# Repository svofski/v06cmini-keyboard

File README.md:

# A miniature keyboard for Vector-06c

The keyboard is a miniature full-functioning replica of Vector-06c keyboard. Its dimensions are 150x55mm. 
It can be connected as a replacement keyboard to the real Vector-06c, or it can be used as a USB HID keyboard with a Vector-06c emulator or FPGA implementation.
It can also be connected to v06c-esp vector-06c-mini.

The design files comprise 3 parts. 

 1. [Key caps](blender) A high resolution mesh with legend engraving designed in blender
 2. [Bottom PCB](kicad/v06ckeyboard) carries the switches and an optional Pi Pico for connectivity
 3. [Top PCB](kicad/v06ckeyboard) a frame that holds the keycaps in place

This keyboard is very small indeed.

## Firmware

### spislave

[spislave](firmware/spislave) is the main intended use with [v06x-mini](https://github.com/svofski/v06x-tiny).

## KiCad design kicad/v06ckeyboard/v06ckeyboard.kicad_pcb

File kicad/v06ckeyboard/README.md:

# vector-06c-mini keyboard PCBs

Main PCB and keycaps frame.

Explore using [kicanvas](https://kicanvas.org/?github=https%3A%2F%2Fgithub.com%2Fsvofski%2Fv06cmini-keyboard%2Ftree%2Fmaster%2Fkicad%2Fv06ckeyboard).

[PDF schematic](/kicad/v06ckeyboard/v06c-mini-keyboard.pdf)

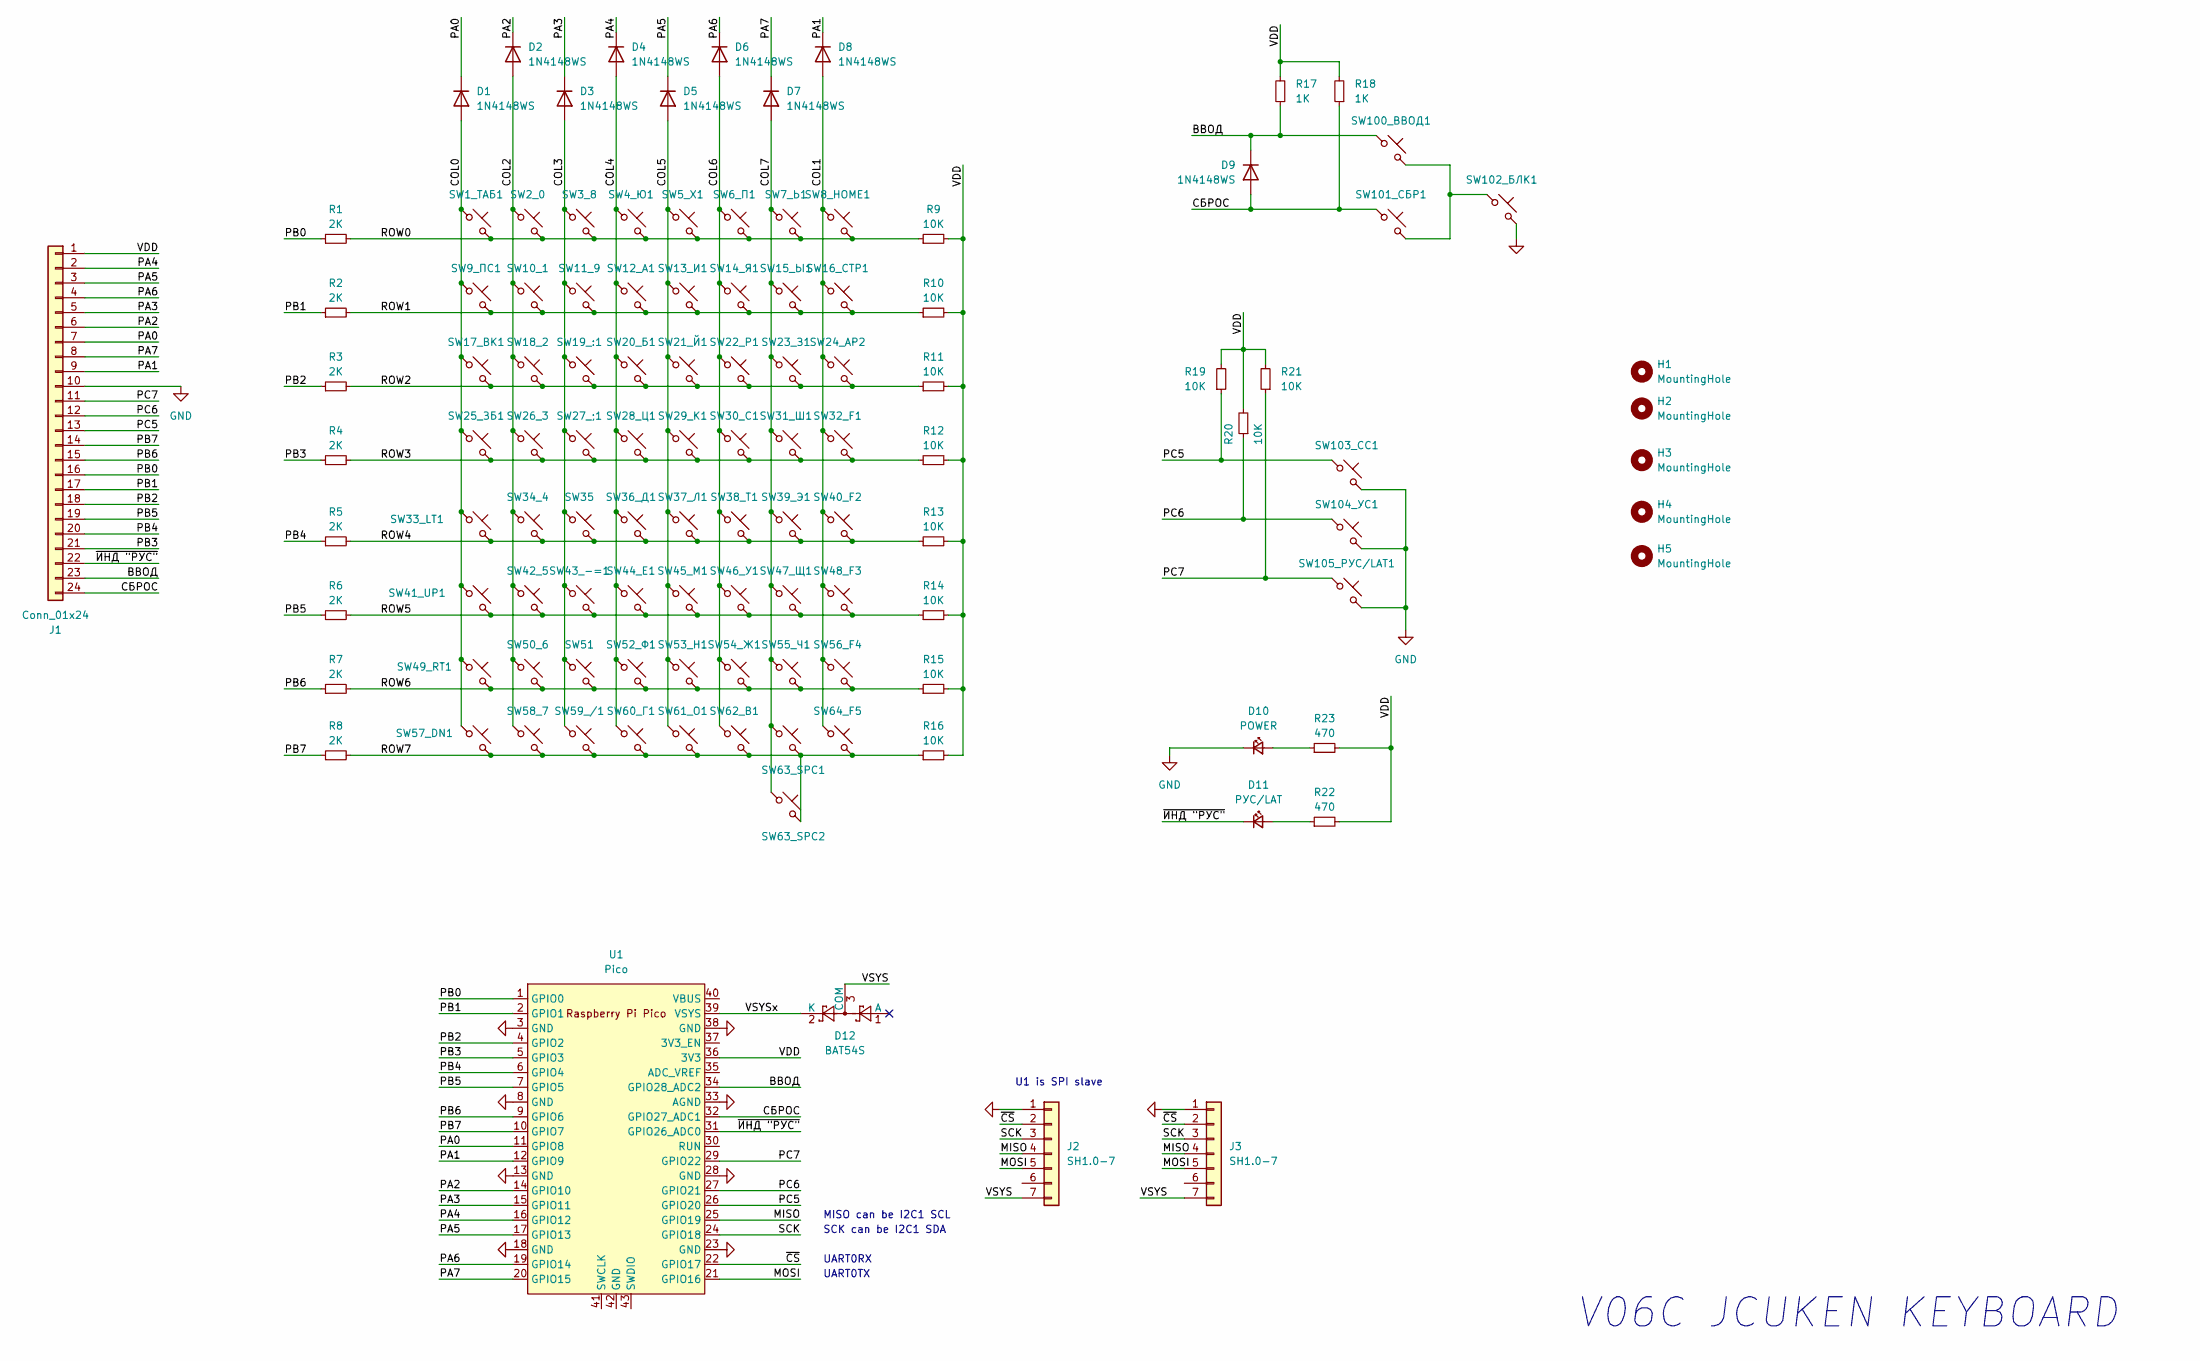
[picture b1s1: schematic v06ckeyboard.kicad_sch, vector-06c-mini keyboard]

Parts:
D1, D2, D3, D4, D5, D6, D7, D8, D9: 1N4148WS; D_SOD-323; LCSC C2128
D10: POWER; LED_0805_2012Metric
D11: РУС/LAT; LED_0805_2012Metric
D12: BAT54S; SOT-23
H1, H2, H3, H4, H5: MountingHole; MountingHole_3.2mm_M3
J1: Conn_01x24; PinHeader_1x24_P2.54mm_Horizontal
J2: SH1.0-7; PinHeader_1x07_P2.54mm_Vertical
J3: SH1.0-7; JST_SH_SM07B-SRSS-TB_1x07-1MP_P1.00mm_Horizontal
R1, R2, R3, R4, R5, R6, R7, R8: 2K; R_0603_1608Metric
R9, R10, R11, R12, R13, R14, R15, R16, R19, R20, R21: 10K; R_0603_1608Metric
R17, R18: 1K; R_0603_1608Metric
R22, R23: 470; R_0603_1608Metric
SW1_ТАБ1, SW2_0, SW3_8, SW4_Ю1, SW5_Х1, SW6_П1, SW7_Ь1, SW8_HOME1, SW9_ПС1, SW10_1, SW11_9, SW12_А1, SW13_И1, SW14_Я1, SW15_Ы1, SW16_СТР1, SW17_ВК1, SW18_2, SW19_:1, SW20_Б1, SW21_Й1, SW22_Р1, SW23_З1, SW24_AP2, SW25_ЗБ1, SW26_3, SW27_;1, SW28_Ц1, SW29_К1, SW30_С1, SW31_Ш1, SW32_F1, SW33_LT1, SW34_4, SW35, SW36_Д1, SW37_Л1, SW38_Т1, SW39_Э1, SW40_F2, SW41_UP1, SW42_5, SW43_-=1, SW44_E1, SW45_М1, SW46_У1, SW47_Щ1, SW48_F3, SW49_RT1, SW50_6, SW51, SW52_Ф1, SW53_Н1, SW54_Ж1, SW55_Ч1, SW56_F4, SW57_DN1, SW58_7, SW59_/1, SW60_Г1, SW61_О1, SW62_В1, SW63_SPC1, SW63_SPC2, SW64_F5, SW100_ВВОД1, SW101_СБР1, SW102_БЛК1, SW103_СС1, SW104_УС1, SW105_РУС/LAT1: SKPMAME010; SKPM; LCSC C115348
U1: Pico; RPi_Pico_SMD_TH

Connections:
/COL0: D1.2 (A), SW1_ТАБ1.1, SW9_ПС1.1, SW17_ВК1.1, SW25_ЗБ1.1, SW33_LT1.1, SW41_UP1.1, SW49_RT1.1, SW57_DN1.1
/COL1: D8.2 (A), SW8_HOME1.1, SW16_СТР1.1, SW24_AP2.1, SW32_F1.1, SW40_F2.1, SW48_F3.1, SW56_F4.1, SW64_F5.1
/COL2: D2.2 (A), SW2_0.1, SW10_1.1, SW18_2.1, SW26_3.1, SW34_4.1, SW42_5.1, SW50_6.1, SW58_7.1
/COL3: D3.2 (A), SW3_8.1, SW11_9.1, SW19_:1.1, SW27_;1.1, SW35.1, SW43_-=1.1, SW51.1, SW59_/1.1
/COL4: D4.2 (A), SW4_Ю1.1, SW12_А1.1, SW20_Б1.1, SW28_Ц1.1, SW36_Д1.1, SW44_E1.1, SW52_Ф1.1, SW60_Г1.1
/COL5: D5.2 (A), SW5_Х1.1, SW13_И1.1, SW21_Й1.1, SW29_К1.1, SW37_Л1.1, SW45_М1.1, SW53_Н1.1, SW61_О1.1
/COL6: D6.2 (A), SW6_П1.1, SW14_Я1.1, SW22_Р1.1, SW30_С1.1, SW38_Т1.1, SW46_У1.1, SW54_Ж1.1, SW62_В1.1
/COL7: D7.2 (A), SW7_Ь1.1, SW15_Ы1.1, SW23_З1.1, SW31_Ш1.1, SW39_Э1.1, SW47_Щ1.1, SW55_Ч1.1, SW63_SPC1.1, SW63_SPC2.1
/MISO: J2.4, J3.4, U1.25 (GPIO19)
/MOSI: J2.5, J3.5, U1.21 (GPIO16)
/PA0: D1.1 (K), J1.7, U1.11 (GPIO8)
/PA1: D8.1 (K), J1.9, U1.12 (GPIO9)
/PA2: D2.1 (K), J1.6, U1.14 (GPIO10)
/PA3: D3.1 (K), J1.5, U1.15 (GPIO11)
/PA4: D4.1 (K), J1.2, U1.16 (GPIO12)
/PA5: D5.1 (K), J1.3, U1.17 (GPIO13)
/PA6: D6.1 (K), J1.4, U1.19 (GPIO14)
/PA7: D7.1 (K), J1.8, U1.20 (GPIO15)
/PB0: J1.16, R1.1, U1.1 (GPIO0)
/PB1: J1.17, R2.1, U1.2 (GPIO1)
/PB2: J1.18, R3.1, U1.4 (GPIO2)
/PB3: J1.21, R4.1, U1.5 (GPIO3)
/PB4: J1.20, R5.1, U1.6 (GPIO4)
/PB5: J1.19, R6.1, U1.7 (GPIO5)
/PB6: J1.15, R7.1, U1.9 (GPIO6)
/PB7: J1.14, R8.1, U1.10 (GPIO7)
/PC5: J1.13, R19.1, SW103_СС1.1, U1.26 (GPIO20)
/PC6: J1.12, R20.1, SW104_УС1.1, U1.27 (GPIO21)
/PC7: J1.11, R21.1, SW105_РУС/LAT1.1, U1.29 (GPIO22)
/ROW0: R1.2, R9.1, SW1_ТАБ1.2, SW2_0.2, SW3_8.2, SW4_Ю1.2, SW5_Х1.2, SW6_П1.2, SW7_Ь1.2, SW8_HOME1.2
/ROW1: R2.2, R10.1, SW9_ПС1.2, SW10_1.2, SW11_9.2, SW12_А1.2, SW13_И1.2, SW14_Я1.2, SW15_Ы1.2, SW16_СТР1.2
/ROW2: R3.2, R11.1, SW17_ВК1.2, SW18_2.2, SW19_:1.2, SW20_Б1.2, SW21_Й1.2, SW22_Р1.2, SW23_З1.2, SW24_AP2.2
/ROW3: R4.2, R12.1, SW25_ЗБ1.2, SW26_3.2, SW27_;1.2, SW28_Ц1.2, SW29_К1.2, SW30_С1.2, SW31_Ш1.2, SW32_F1.2
/ROW4: R5.2, R13.1, SW33_LT1.2, SW34_4.2, SW35.2, SW36_Д1.2, SW37_Л1.2, SW38_Т1.2, SW39_Э1.2, SW40_F2.2
/ROW5: R6.2, R14.1, SW41_UP1.2, SW42_5.2, SW43_-=1.2, SW44_E1.2, SW45_М1.2, SW46_У1.2, SW47_Щ1.2, SW48_F3.2
/ROW6: R7.2, R15.1, SW49_RT1.2, SW50_6.2, SW51.2, SW52_Ф1.2, SW53_Н1.2, SW54_Ж1.2, SW55_Ч1.2, SW56_F4.2
/ROW7: R8.2, R16.1, SW57_DN1.2, SW58_7.2, SW59_/1.2, SW60_Г1.2, SW61_О1.2, SW62_В1.2, SW63_SPC1.2, SW63_SPC2.2, SW64_F5.2
/SCK: J2.3, J3.3, U1.24 (GPIO18)
/VDD: J1.1, R9.2, R10.2, R11.2, R12.2, R13.2, R14.2, R15.2, R16.2, R17.2, R18.2, R19.2, R20.2, R21.2, R22.2, R23.2, U1.36 (3V3)
/VSYS: D12.3 (COM), J2.7, J3.7
/VSYSx: D12.2 (K), U1.39 (VSYS)
/~CS: J2.2, J3.2, U1.22 (GPIO17)
/~ИНД "РУС": D11.1 (K), J1.22, U1.31 (GPIO26_ADC0)
/ВВОД: D9.1 (K), J1.23, R17.1, SW100_ВВОД1.1, U1.34 (GPIO28_ADC2)
/СБРОС: D9.2 (A), J1.24, R18.1, SW101_СБР1.1, U1.32 (GPIO27_ADC1)
GND: D10.1 (K), J1.10, J2.1, J3.1, SW102_БЛК1.2, SW103_СС1.2, SW104_УС1.2, SW105_РУС/LAT1.2, U1.3 (GND), U1.8 (GND), U1.13 (GND), U1.18 (GND), U1.23 (GND), U1.28 (GND), U1.33 (AGND), U1.38 (GND)
unnamed: D10.2 (A), R23.1
unnamed: D11.2 (A), R22.1
unnamed: SW100_ВВОД1.2, SW101_СБР1.2, SW102_БЛК1.1

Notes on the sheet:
V06C JCUKEN KEYBOARD
UART0TX
MISO can be I2C1 SCL
UART0RX
SCK can be I2C1 SDA
U1 is SPI slave

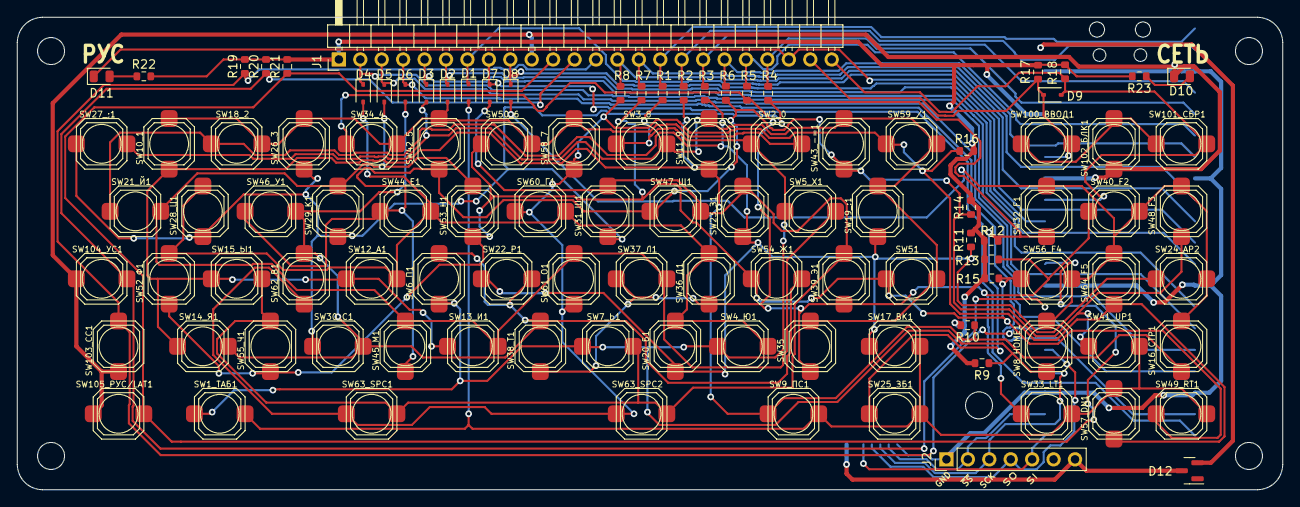
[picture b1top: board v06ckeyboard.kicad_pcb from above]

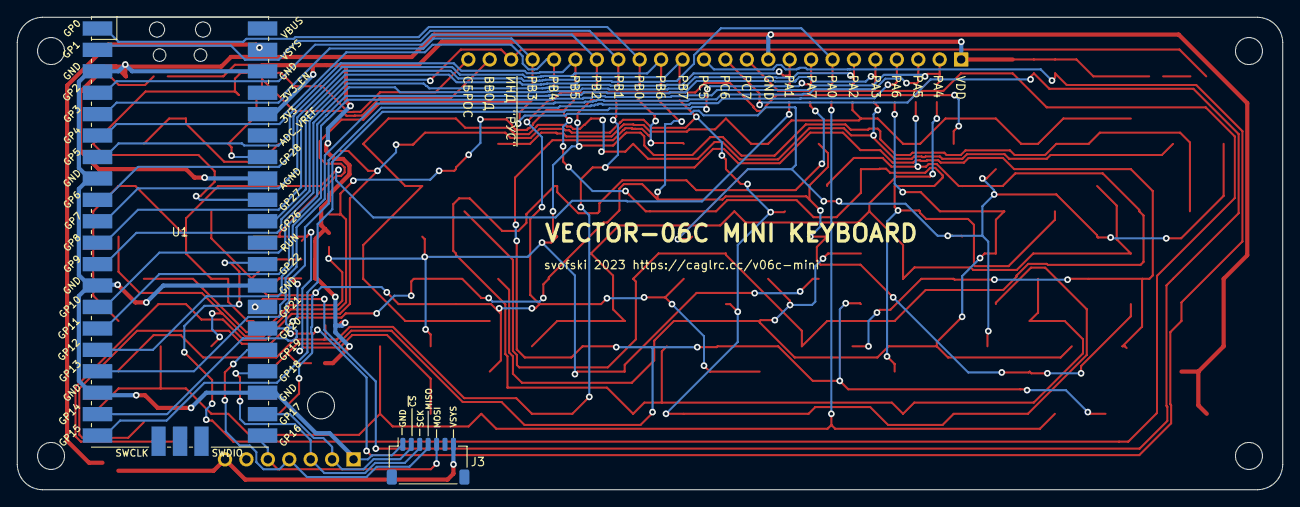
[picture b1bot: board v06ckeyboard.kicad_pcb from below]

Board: 2 copper layers, 150.0 x 56.0 mm, 115 parts (2 on the bottom side), 49 nets.

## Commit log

2023-11-03 frist commit
2023-11-03 more files
2023-11-03 added schematic pdf
2023-11-04 photo updated
2023-11-16 added spislave
2023-11-16 readme lala
2023-11-19 rp2040 spi slave is bullshit
